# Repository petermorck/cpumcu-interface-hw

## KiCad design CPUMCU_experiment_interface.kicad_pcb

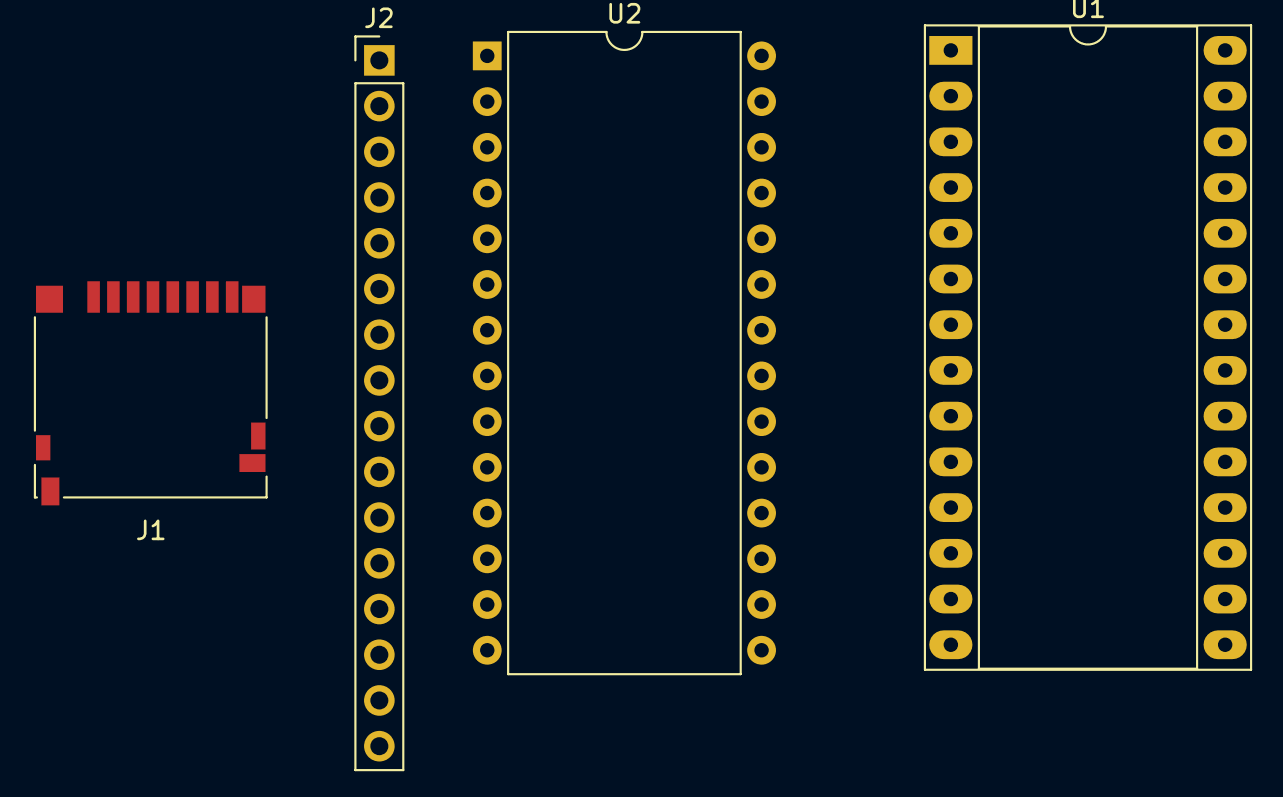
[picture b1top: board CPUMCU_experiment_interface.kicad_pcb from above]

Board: 2 copper layers, 4 parts (0 on the bottom side), 16 nets, no tracks yet.

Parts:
J1: Micro_SD_Card_Det_Hirose_DM3AT; microSD_HC_Hirose_DM3D-SF
J2: LCD Connector; PinHeader_1x16_P2.54mm_Vertical
U1: 6581SID; DIP-28_W15.24mm_Socket_LongPads
U2: 27C256; DIP-28_W15.24mm

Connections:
+5V: J2.2, U1.25, U2.1, U2.28
/A0: U1.9, U2.10
/A1: U1.10, U2.9
/A2: U1.11, U2.8
/A3: U1.12, U2.7
/A4: U1.13, U2.6
/D0: J2.7, U1.15, U2.11
/D1: J2.8, U1.16, U2.12
/D2: J2.9, U1.17, U2.13
/D3: J2.10, U1.18, U2.15
/D4: J2.11, U1.19, U2.16
/D5: J2.12, U1.20, U2.17
/D6: J2.13, U1.21, U2.18
/D7: J2.14, U1.22, U2.19
/R~W: J2.5, U1.7
GND: J2.1, U1.14, U2.14, U2.20

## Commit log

2018-11-08 Initial commit
    Just the SID symbol created, added to the schematic along with
    some LCD pinheader.
2018-11-16 Added EPROM and temporary microSD card reader
    microSD card reader will probably be replaced.
2019-05-05 Added 8 SPST switches
    Added 8 SPST switches and an 8-resistor array.
